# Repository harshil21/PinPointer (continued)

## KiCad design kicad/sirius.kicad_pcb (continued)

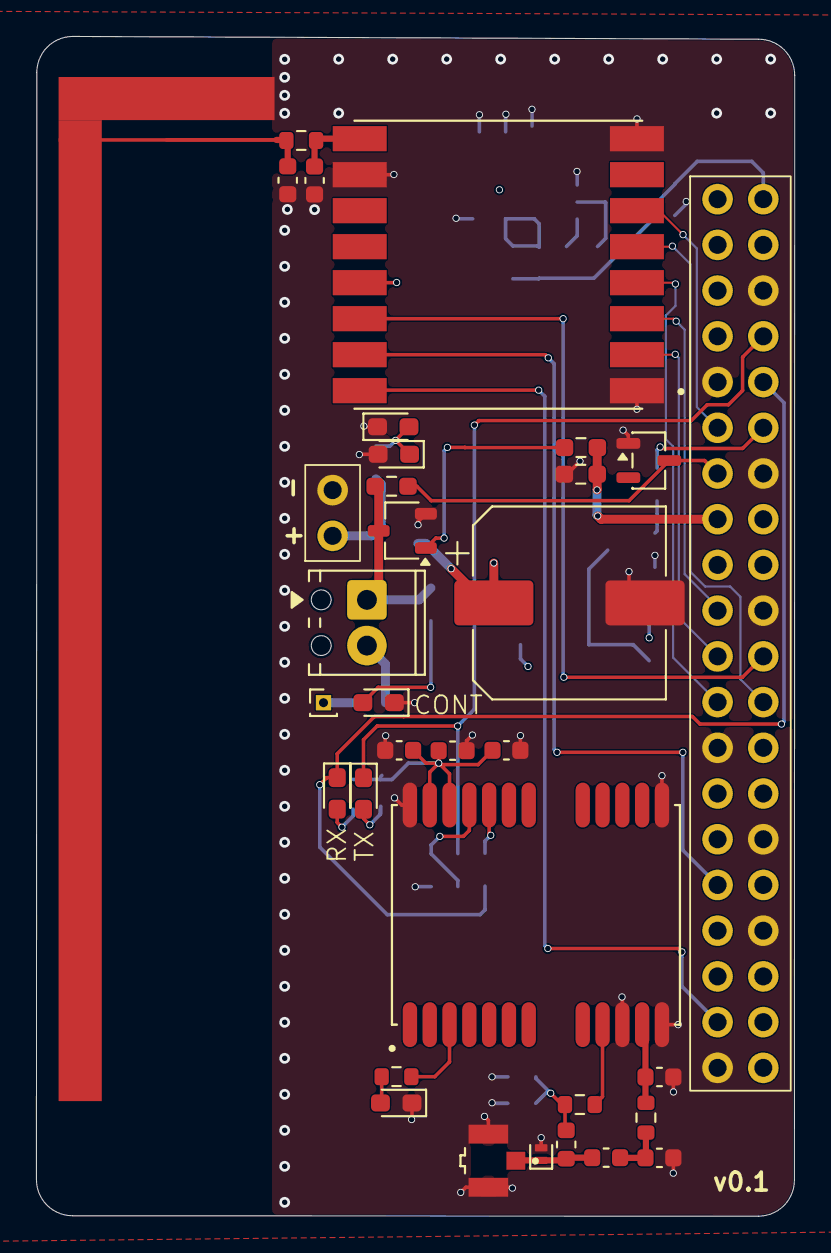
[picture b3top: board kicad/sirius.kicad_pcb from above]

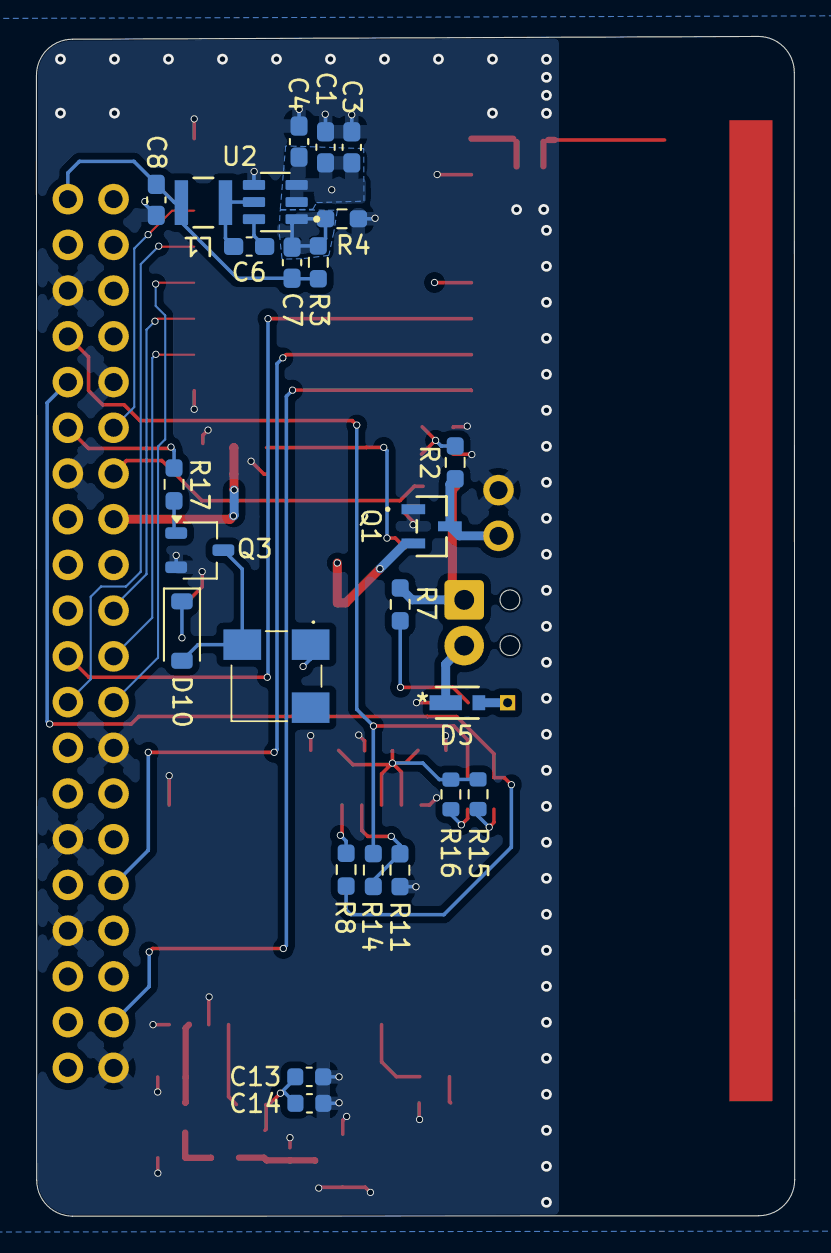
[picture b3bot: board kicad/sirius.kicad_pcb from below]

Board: 4 copper layers, 42.1 x 65.5 mm, 59 parts (25 on the bottom side), 42 nets.

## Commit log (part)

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2025-08-21 Mention project goals
2025-09-25 Add radio telemetry testing script (transmitter)
2025-09-25 Debugging SPI
2025-09-25 Successfully debugged SPI
2025-09-26 More debug
2025-09-26 Try using spidev in rfm95 library
2025-09-26 Add receiver script
2025-09-27 Backlink to CADLAB.io has been added.
2025-10-08 WIP Rust code
2025-10-09 Add display behaviour
2025-10-12 Update kicad custom symbols, footprints, 3d models
2025-10-13 Work on schematic some more
2025-10-20 Work on schematic some more, only thing left is screw switch
2026-03-20 In progress Sirius PCB design
2026-03-21 Try to manually simulate
2026-03-21 Very close to 915Mhz resonance, not impendance matched though
    Had to increase board width though
2026-03-21 Clean up some sim results, add temp openems examples
2026-03-21 Perfect resonance at 915MHz, -35dB S11
2026-03-21 Slight tuning
2026-03-22 Refactor to use classes
2026-04-01 Refactor to use classes properly
    Recompile openEMS with boost 1.90 and link wheels. Also update the PCB with the antenna. Still unrouted
2026-04-01 Add the 915 Mhz footprint, update gitignore
    Also use kicad v10 (in the last commit)
2026-04-01 New simulation: 15Mhz bandwidth, -42.4dB S11, more feed sep, no meander
2026-04-02 Add support for vias in simulation, use 0.2mm keepout
2026-04-02 Add support for 4 layer board. This shifts center freq to 923Mhz
2026-04-07 Finish Sirius PCB design
    Logo pending
2026-04-07 Pass DRC, fix IFA net tie, restructure sirius and sopdet
2026-04-07 Finish Sopdet schematic
2026-04-08 Finish routing Sopdet
    Logo still pending
2026-04-09 Finish Sopdet routing
    Also add logos for Sirius and Sopdet
2026-04-09 Replace footprint of u.fl connector & screw terminal
    Redesign board to accomodate larger footprint, make Sopdet a little smaller to qualify for $2 jlcpcb price, assign Digikey PN to all components, add a script which combines the BOM's of both boards s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
2026-04-17 Add script for yagi antenna simulation
2026-04-18 Update openrocket with real rocket dimensions
    Use estimated payload mass for now
2026-04-18 Port code from MAARCO to Pinpointer
2026-04-20 no default features for serialport
2026-04-20 Update transmit python script
2026-04-20 Rename rtkbase, add rfm95 library
2026-04-20 Update receive python script
2026-04-20 Update send and receive rust script
2026-04-22 Update openrocket with overriden masses
2026-04-26 Add code for rocket and ground station
2026-05-02 Add missing datasheet link
2026-05-02 Change log name to logs/log_hh_mm_ss
    Add firm client python script
2026-05-02 Change port
2026-05-02 add firm reboot script
2026-05-06 Make sirius log in logs/
2026-05-07 Add GPS SNR capability
    Also update IP address in cargo-shipit config
2026-05-07 First Claude pass with Android app
2026-05-07 Settings page, some theme fixes
2026-05-11 WIP: Doesn't build atm, adding new command for debug telemetry
2026-05-11 Display rocket debug SNR in Android; consolidate spammy info logs
    Root cause for missing Android display: the sopdet HTTP status payload
    already exposes per-constellation SNR from the rocket via
    `rocket_debug_snr`, and `StatusJson` already deserialised it, but the
    Android UI only used the field as a presence flag for the
    "Debug telemetry: ACTIVE" indicator on the Commands screen — it never
    rendered the actual values anywhere.
2026-05-11 Update sirius.json ip
2026-05-28 Increase decimal precision on GPS
2026-05-28 Update openrocket with recovery masses
    Also fix the fins mass to the middle centering ring
2026-05-31 Refine CoM location for fin can
2026-06-06 Update openrocket with new masses and lengths
    Pending correct mass update for nosecone and bulkhead with altimeter wires
2026-06-06 Update state changes, use musl target
2026-06-07 Update rocket masses
2026-06-07 Use absolute paths for logs, fix buzzer using random LoRa packets
2026-06-08 do time sync for log file names
2026-06-09 Add z-clip, update rocket length
2026-06-13 Final rocket masses and code
2026-06-13 Change state constants, make pyro channel fire thrice
2026-06-13 Openrocket didn't save
2026-06-20 WIP: Start making new version of Sirius
2026-06-23 Finish Sirius v0.2
2026-06-30 Add command for zeroing out pressure altitude
    Also update logs with truncation and remove rx_packet_hex field from being logged
2026-06-30 Add command for setting radio Tx power in Sopdet, Sirius, and android app
